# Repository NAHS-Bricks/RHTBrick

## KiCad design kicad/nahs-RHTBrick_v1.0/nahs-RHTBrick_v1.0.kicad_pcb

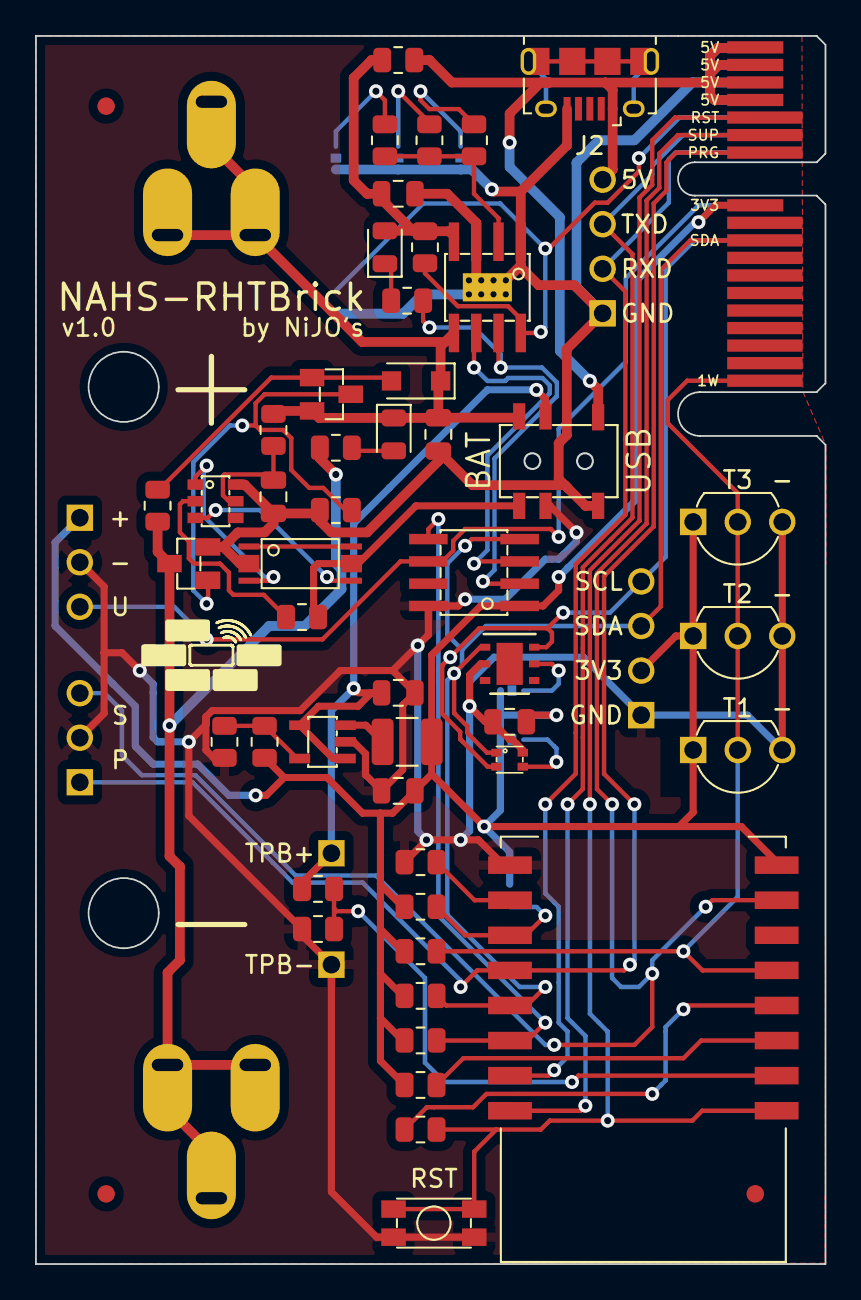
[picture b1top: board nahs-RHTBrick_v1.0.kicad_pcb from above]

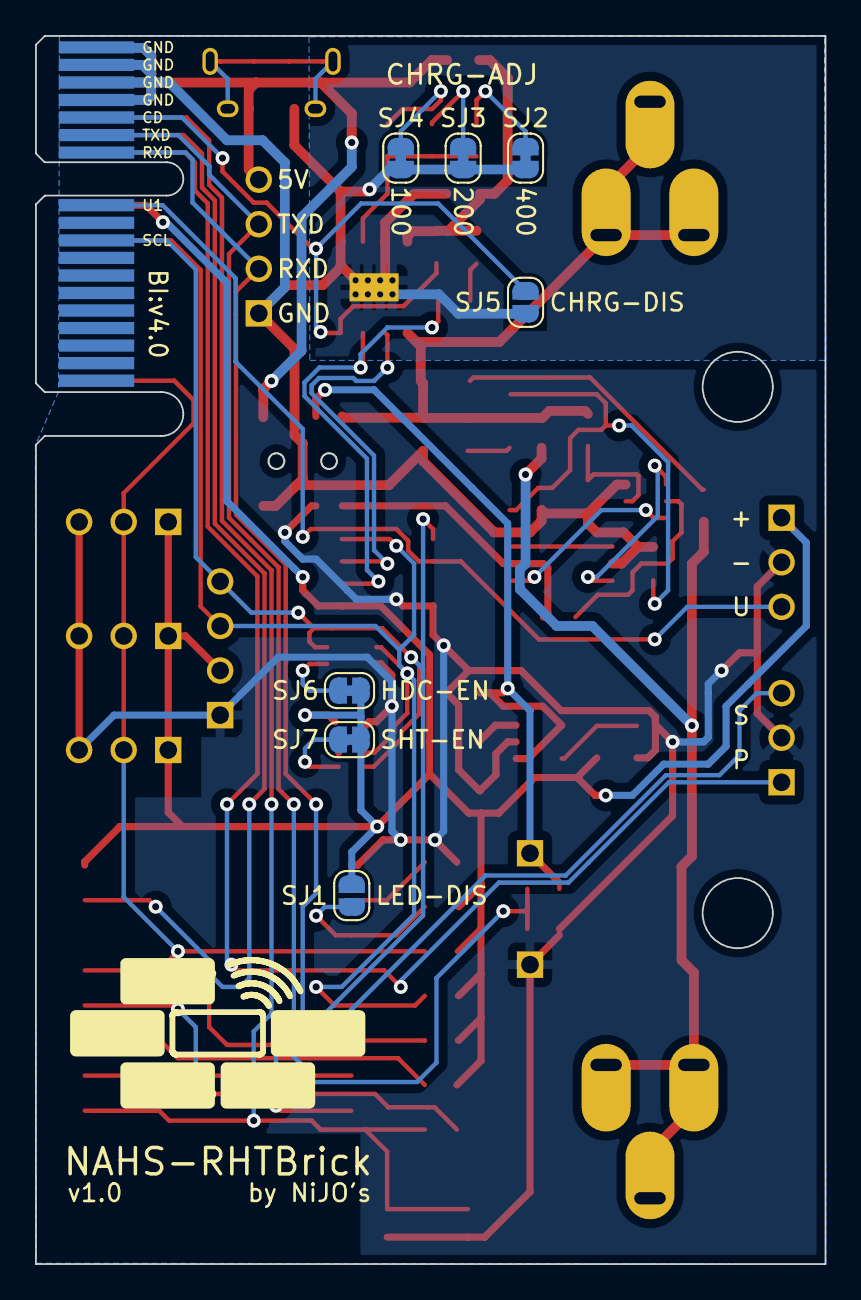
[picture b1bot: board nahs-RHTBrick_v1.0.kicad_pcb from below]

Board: 2 copper layers, 45.0 x 70.0 mm, 68 parts (8 on the bottom side), 43 nets.

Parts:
BT: HA_18650_EK
C1, C1#2, C1#3, C1#4, C1#5, C1#6: 100nF; C_0805_2012Metric
D1: 1N4148WL; D_SOD-123F
FID1, FID2, FID3: Fiducial; Fiducial_1mm_Mask2mm
IC1: ESP12S
IC?: ATTINY212; SOIC8
J: Brick-Interface-V4; Brick_Interface_V4_inset
J2: USB_B_Mini; USB_Micro-B_Amphenol_10118194_Horizontal
JP1, JP5: PINHD_1X03; PINHD_1X03_2.54_1mm_Round
JP1#2: RHT-ALT; PINHD_1X04_2.54_1mm_Round
JP2: PINHD_1X04; PINHD_1X04_2.54_1mm_Round
JP3, JP4: PINHD_1X01; PINHD_1X01_2.54_1mm_Square
JP6, JP7, JP8: PINHD_1X03; PINHD_1X03_2.54_1mm_DS18B20
L1: 2.2µH; L_1210_3225Metric
LED1: Green; LED_0805_2012Metric
LED2: Red; LED_0805_2012Metric
LOGO1: brick_logo; x8mm
LOGO2: brick_logo; x17mm
Q1: 8205A; TSSOP8_MS
Q3: CJ2302; SOT23
Q4: MMBT2907A; SOT23
R1, R5, R6: 3.9k; R_0805_2012Metric
R2, R11, R14, R17: 1k; R_0805_2012Metric
R3, R4, R7, R13, R18, R19: 10k; R_0805_2012Metric
R8: 2.7M; R_0805_2012Metric
R9, R21: 590k; R_0805_2012Metric
R10: 100; R_0805_2012Metric
R12: 0.4; R_0805_2012Metric
R15: 3k; R_0805_2012Metric
R20: 130k; R_0805_2012Metric
R22: 6,04k; R_0805_2012Metric
R23: 12k; R_0805_2012Metric
SJ1, SJ1#3, SJ1#4, SJ1#5, SJ1#7: RHT-ALT; SolderJumper-2_P1.3mm_Bridged_RoundedPad1.0x1.5mm
SJ1#2, SJ1#6: LED-DIS; SolderJumper-2_P1.3mm_Open_RoundedPad1.0x1.5mm
SW1: KMR_231_G_LFS
SW2: SSSS820101
U1: ZD8028IB5TR; SOT23-5
U2: HDC1080; Texas_PWSON-N6
U3: DW01A; SOT23-6
U4: TP4056; SOIC8_TP
U5: SHT40A; SHT4xA

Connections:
1WIRE: IC1.5 (D5), J.B1 (UTIL1), JP6.2, JP7.2, JP8.2, R1.2
+3V3: C1#3.1, C1#4.1, IC1.8 (VCC), IC?.1 (VCC), J.B11 (3.3V), JP1#2.2, JP5.1, JP6.1, JP7.1, JP8.1, L1.2, R1.1, R3.1, R4.1, R5.1, R6.1, R21.2, SJ1#3.2 (B), SJ1#4.2 (B), SJ1#6.1 (A)
/CHRG+: C1.1, LED1.2 (A), R12.1, R13.1, U4.4 (VCC)
A0: IC1.2 (ADC), R8.2, R9.1
BAT+: BT.P (+), C1#5.1, D1.1 (K), LED2.1 (K), Q4.2 (E), R10.2, SW2.6, U4.5 (BAT)
BAT-: BT.M (-), Q3.3 (D), R17.2, R19.1
BOOT1: IC1.17 (D4), R4.2, SJ1#6.2 (B)
BOOT2: IC1.16 (D8), R7.2
CD: J.A14 (CD), R13.2, SJ1#2.2 (B), U4.8 (CE)
CHRG: IC?.2 (PA6), R14.2, U4.7 (CHRG)
EN: IC1.3 (EN), R3.2
GND: C1#2.2, C1#3.2, C1#4.2, IC1.15 (GND), IC?.8 (GND), JP1.2, JP1#2.1, JP4.1, JP5.2, JP6.3, JP7.3, JP8.3, R7.1, R9.2, R20.1, SW1.1, SW1.2, SW2.2, U1.2 (GND), U2.2 (GND), U5.4 (GND)
IN+: J.B15 (5V), J.B16 (5V), J.B17 (5V), J.B18 (5V), J2.1 (VBUS), JP2.4, R12.2, SW2.4
IN-: C1.2, C1#5.2, C1#6.2, J.A15 (GND), J.A16 (GND), J.A17 (GND), J.A18 (GND), J2.5 (GND), JP2.1, Q1.2 (S1), Q3.2 (S), R18.1, SJ1.1 (A), SJ1#2.1 (A), SJ1#5.1 (A), SJ1#7.1 (A), SW2.3, U3.6 (GND), U4.1 (TEMP), U4.3 (GND), U4.T1 (GND), U4.T2 (GND), U4.T3 (GND), U4.T4 (GND), U4.T5 (GND), U4.T6 (GND), U4.T7 (GND), U4.T8 (GND)
unnamed: C1#6.1, R10.1, U3.5 (VCC)
unnamed: D1.2 (A), Q4.1 (B), R19.2
unnamed: IC1.4 (D0), R2.1
unnamed: L1.1, U1.3 (SW)
unnamed: LED1.1 (K), R14.1
unnamed: LED2.2 (A), R17.1
unnamed: Q1.3 (G1), U3.1 (OD)
unnamed: Q1.4 (G2), U3.3 (OC)
unnamed: Q1.1 (D1), Q1.6 (D2)
unnamed: Q3.1 (G), Q4.3 (C), R18.2
unnamed: R11.2, U3.2 (CS)
unnamed: R15.1, SJ1.2 (B)
unnamed: R15.2, R22.2, R23.2, U4.2 (PROG)
unnamed: R20.2, R21.1, U1.5 (FB)
unnamed: R22.1, SJ1#5.2 (B)
unnamed: R23.1, SJ1#7.2 (B)
unnamed: SJ1#4.1 (A), U2.5 (VCC)
unnamed: SJ1#3.1 (A), U5.3 (VCC)
PROG: IC1.18 (D3), J.B12 (PROG), JP1.1
PRT-: Q1.5 (S2), R11.1, SW2.1
RST: IC1.1 (~RST), J.B14 (RST), R2.2, SW1.3, SW1.4
RXD: IC1.21 (RXD0), J.A12 (RX), JP2.2
SCL: IC1.20 (D1), IC?.5 (PA2), J.A9 (SCL), JP1#2.4, R6.2, U2.6 (SCL), U5.2 (SCL)
SDA: IC1.19 (D2), IC?.4 (PA1), J.B9 (SDA), JP1#2.3, R5.2, U2.1 (SDA), U5.1 (SDA)
SEL+: C1#2.1, JP3.1, R8.1, SW2.5, U1.1 (EN), U1.4 (IN)
SETUP: IC1.7 (D7), J.B13 (SETUP), JP1.3
STDBY: IC?.3 (PA7), U4.6 (STDBY)
TXD: IC1.22 (TXD0), J.A13 (TX), JP2.3
UPDI: IC?.6 (RST/UPDI), J.A11 (UPDI1), JP5.3

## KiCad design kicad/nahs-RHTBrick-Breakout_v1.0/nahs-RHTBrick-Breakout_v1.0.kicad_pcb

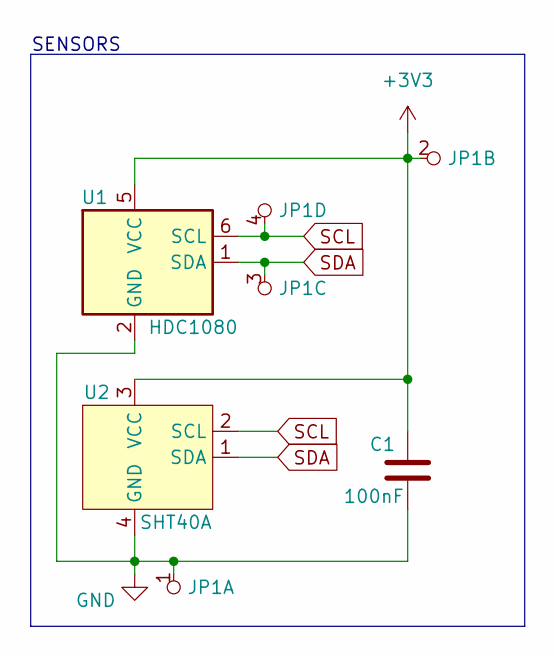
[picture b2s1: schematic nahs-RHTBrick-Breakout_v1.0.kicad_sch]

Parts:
C1: 100nF; C_0805_2012Metric
JP1: RHT-ALT; PINHD_1X04_2.54_1mm_Round
U1: HDC1080; Texas_PWSON-N6
U2: SHT40A; SHT4xA

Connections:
+3V3: C1.1, JP1.2, U1.5 (VCC), U2.3 (VCC)
GND: C1.2, JP1.1, U1.2 (GND), U2.4 (GND)
SCL: JP1.4, U1.6 (SCL), U2.2 (SCL)
SDA: JP1.3, U1.1 (SDA), U2.1 (SDA)

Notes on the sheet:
SENSORS

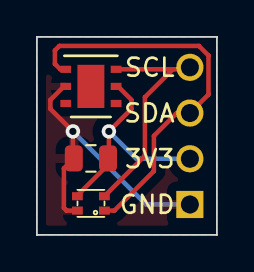
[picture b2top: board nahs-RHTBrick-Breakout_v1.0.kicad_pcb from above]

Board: 2 copper layers, 10.0 x 11.0 mm, 4 parts (0 on the bottom side), 4 nets.

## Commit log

2021-08-09 begun v1.0 R1 Board
2021-08-09 saving
2021-08-10 v1.0 R1 Board done
2021-09-24 platformio project for v1 board
2021-10-05 v1.0 R2 Board
2021-10-14 v1.0 R2 Board done
2022-01-13 build-firmware invoker
2022-02-13 added ibom invoker and ibom for v1.0 r board
2022-12-01 v1.0 R3 Board done
2022-12-03 v1.0 R4 Board done
2022-12-03 added forgotten logo on v1.0 R4 Board
2022-12-09 replaced footprints with ones with custom paste mask on v1.0 R4 Board
2022-12-11 migrated firmware to new librarys
2022-12-30 started design of final v1.0 board
2023-01-02 forced firmware dependencies to support SHT4x sensors
2023-01-05 v1.0 Board - adjustments on bottom layer silkscreen
2024-01-11 v1.0 Board done; v1.0 Breakout Board done
2024-01-11 updated footprints for stencil
